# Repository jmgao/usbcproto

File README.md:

usbcproto
=============

A simple STM32F103 protoboard with an on-PCB USB-C connector.

The USB-C footprint is from Pinuct's [Eagle PCB USB connectors](https://github.com/Pinuct/Eagle_PCB_USB_connectors).

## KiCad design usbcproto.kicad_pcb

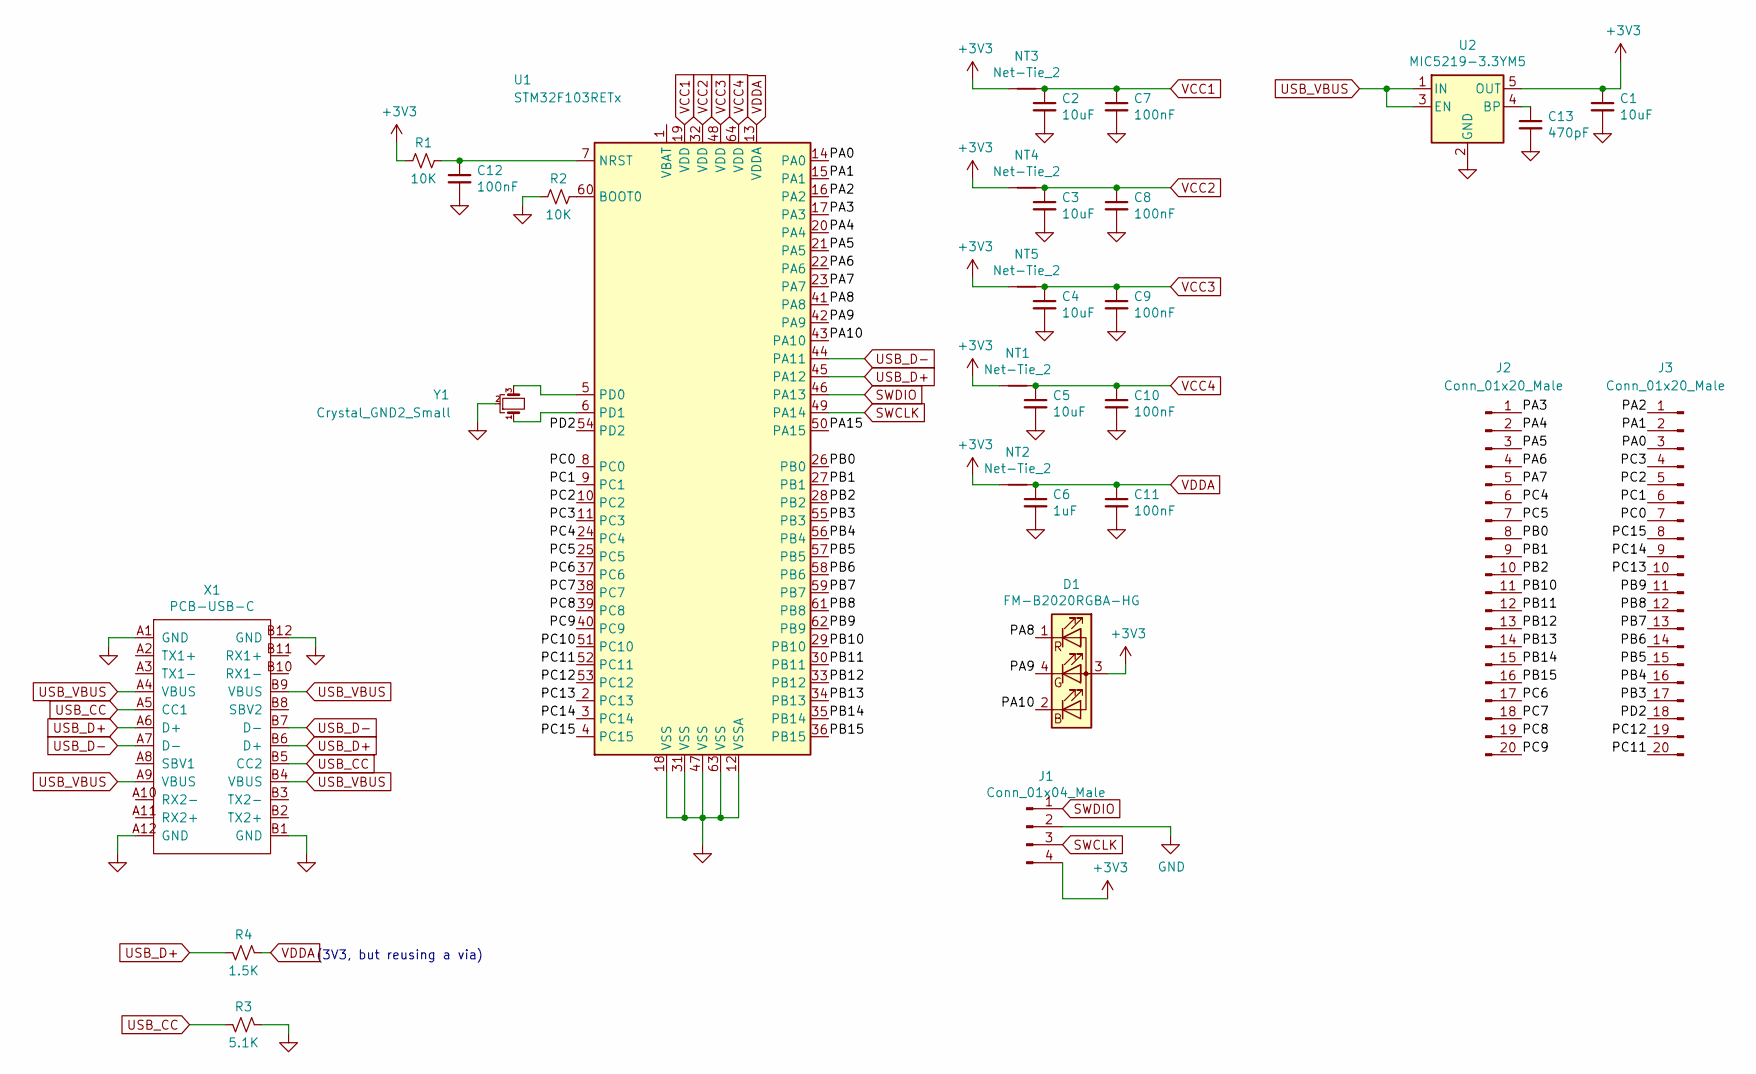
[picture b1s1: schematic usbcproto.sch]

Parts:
C1, C2, C3, C4, C5: 10uF; C_0603_1608Metric
C6: 1uF; C_0603_1608Metric
C7, C8, C9, C10, C11, C12: 100nF; C_0603_1608Metric
C13: 470pF; C_0603_1608Metric
D1: FM-B2020RGBA-HG
J1: Conn_01x04_Male; PinHeader_1x04_P1.27mm_Vertical
J2, J3: Conn_01x20_Male; PinHeader_1x20_P1.27mm_Vertical
NT1, NT2, NT3, NT4, NT5: Net-Tie_2; NetTie-2_SMD_Pad0.5mm
R1, R2: 10K; R_0603_1608Metric
R3: 5.1K; R_0603_1608Metric
R4: 1.5K; R_0603_1608Metric
U1: STM32F103RETx; LQFP-64_10x10mm_P0.5mm
U2: MIC5219-3.3YM5; SOT-23-5
X1: PCB-USB-C
Y1: Crystal_GND2_Small; Resonator_SMD_muRata_CSTxExxV-3Pin_3.0x1.1mm

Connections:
+3V3: C1.1, D1.3 (+), J1.4, NT1.1, NT2.1, NT3.1, NT4.1, NT5.1, R1.2, U2.5 (OUT)
/PA0: J3.3, U1.14 (PA0)
/PA1: J3.2, U1.15 (PA1)
/PA2: J3.1, U1.16 (PA2)
/PA3: J2.1, U1.17 (PA3)
/PA4: J2.2, U1.20 (PA4)
/PA5: J2.3, U1.21 (PA5)
/PA6: J2.4, U1.22 (PA6)
/PA7: J2.5, U1.23 (PA7)
/PA8: D1.1 (R-), U1.41 (PA8)
/PA9: D1.4 (G-), U1.42 (PA9)
/PA10: D1.2 (B-), U1.43 (PA10)
/PA15: U1.50 (PA15)
/PB0: J2.8, U1.26 (PB0)
/PB1: J2.9, U1.27 (PB1)
/PB2: J2.10, U1.28 (PB2)
/PB3: J3.17, U1.55 (PB3)
/PB4: J3.16, U1.56 (PB4)
/PB5: J3.15, U1.57 (PB5)
/PB6: J3.14, U1.58 (PB6)
/PB7: J3.13, U1.59 (PB7)
/PB8: J3.12, U1.61 (PB8)
/PB9: J3.11, U1.62 (PB9)
/PB10: J2.11, U1.29 (PB10)
/PB11: J2.12, U1.30 (PB11)
/PB12: J2.13, U1.33 (PB12)
/PB13: J2.14, U1.34 (PB13)
/PB14: J2.15, U1.35 (PB14)
/PB15: J2.16, U1.36 (PB15)
/PC0: J3.7, U1.8 (PC0)
/PC1: J3.6, U1.9 (PC1)
/PC2: J3.5, U1.10 (PC2)
/PC3: J3.4, U1.11 (PC3)
/PC4: J2.6, U1.24 (PC4)
/PC5: J2.7, U1.25 (PC5)
/PC6: J2.17, U1.37 (PC6)
/PC7: J2.18, U1.38 (PC7)
/PC8: J2.19, U1.39 (PC8)
/PC9: J2.20, U1.40 (PC9)
/PC10: U1.51 (PC10)
/PC11: J3.20, U1.52 (PC11)
/PC12: J3.19, U1.53 (PC12)
/PC13: J3.10, U1.2 (PC13)
/PC14: J3.9, U1.3 (PC14)
/PC15: J3.8, U1.4 (PC15)
/PD2: J3.18, U1.54 (PD2)
GND: C1.2, C2.2, C3.2, C4.2, C5.2, C6.2, C7.2, C8.2, C9.2, C10.2, C11.2, C12.2, C13.2, J1.2, R2.2, R3.2, U1.12 (VSSA), U1.18 (VSS), U1.31 (VSS), U1.47 (VSS), U1.63 (VSS), U2.2 (GND), X1.A1 (GND), X1.A12 (GND), X1.B1 (GND), X1.B12 (GND), Y1.2
unnamed: C12.1, R1.1, U1.7 (NRST)
unnamed: C13.1, U2.4 (BP)
unnamed: R2.1, U1.60 (BOOT0)
unnamed: U1.5 (PD0), Y1.3
unnamed: U1.6 (PD1), Y1.1
SWCLK: J1.3, U1.49 (PA14)
SWDIO: J1.1, U1.46 (PA13)
USB_CC: R3.1, X1.A5 (CC1), X1.B5 (CC2)
USB_D+: R4.1, U1.45 (PA12), X1.A6 (D+), X1.B6 (D+)
USB_D-: U1.44 (PA11), X1.A7 (D-), X1.B7 (D-)
USB_VBUS: U2.1 (IN), U2.3 (EN), X1.A4 (VBUS), X1.A9 (VBUS), X1.B4 (VBUS), X1.B9 (VBUS)
VCC1: C2.1, C7.1, NT3.2, U1.19 (VDD)
VCC2: C3.1, C8.1, NT4.2, U1.32 (VDD)
VCC3: C4.1, C9.1, NT5.2, U1.48 (VDD)
VCC4: C5.1, C10.1, NT1.2, U1.64 (VDD)
VDDA: C6.1, C11.1, NT2.2, R4.2, U1.13 (VDDA)

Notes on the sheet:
(3V3, but reusing a via)

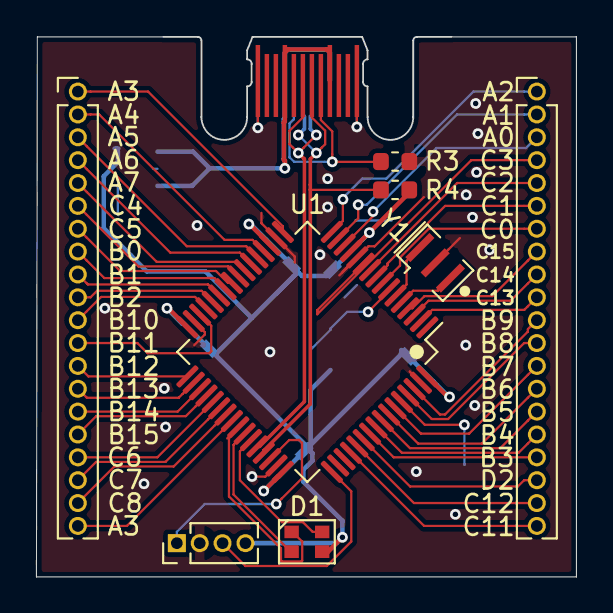
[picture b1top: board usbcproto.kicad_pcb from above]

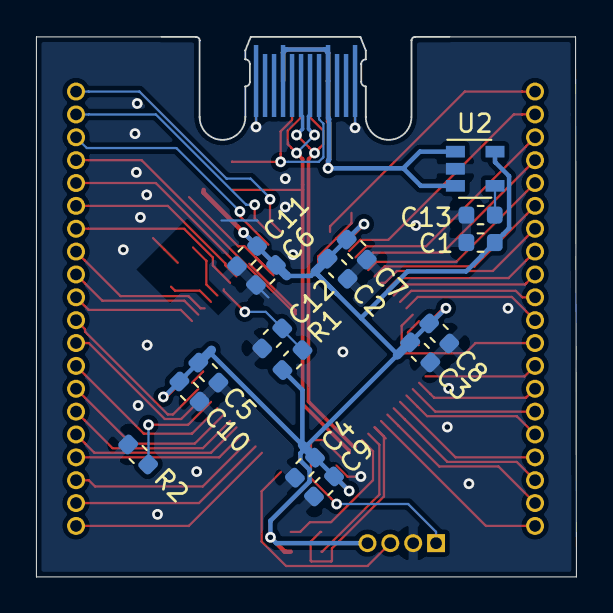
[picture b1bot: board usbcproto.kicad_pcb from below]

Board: 2 copper layers, 30.0 x 30.0 mm, 30 parts (21 on the bottom side), 61 nets.

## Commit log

2019-08-16 Initial commit of barebones board.
2019-08-19 Move PCB-USB-C into a subdirectory.
2019-08-19 Add *.sch-bak to gitignore.
2019-08-19 Add a footprint/symbol for the FM-B2020RGBA-HG.
2019-08-19 Route pins and RGB LED.
